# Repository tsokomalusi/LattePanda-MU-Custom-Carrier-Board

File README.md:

# LattePanda MU Custom Carrier Board

## High Speed PCB Design in KiCad

This repository contains a high-speed PCB design practice project created in KiCad
as part of the High Speed Design with KiCad course by D. Peter Dalmaris.

The primary goal of this project was to gain practical experience with modern
high-speed PCB layout techniques, signal integrity awareness, PCB stackup planning,
and manufacturability considerations.

# Project Background

The project workflow was inspired by the DFRobot LattePanda MU Carrier Board.

As part of the learning process:

- Existing PCB design constraints were studied
- PCB stackup parameters were imported into KiCad
- Routing practices from the reference design were analyzed
- High-speed layout techniques were explored through practical implementation
- Differential pair routing and length tuning techniques were practiced
- Teardrops were implemented throughout the PCB design process

PCIe functionality was not implemented, as the primary focus of the project
was PCB layout practice, signal routing exposure, and understanding high-speed
design workflows.

# 3D PCB Views

## Top Side

## Bottom Side

## Overview

# Technologies & Concepts

 USB 3.0 high-speed routing
- HDMI interface routing
- Gigabit Ethernet routing
- M.2 connector integration
- Differential pair routing and length tuning
- Controlled impedance awareness
- PCB stackup planning
- Return path considerations
- Teardrop implementation
- DFM analysis using NextPCB HQDFM tools

## Design Goals

The project focused on learning and applying:

- High-speed routing practices
- Differential pair management
- Signal integrity fundamentals
- PCB stackup awareness
- Manufacturability considerations

# PCB Stackup & Impedance Planning

The PCB stackup and impedance calculations were reviewed using the NextPCB
impedance calculator and stackup tools.

## Impedance Calculator

## NextPCB Stackup : Huaqiu04161H03-7628

## KiCad Stackup Configuration

## PCB Layout

### Full PCB Overview

# High-Speed Routing Examples

### USB 3.0 Routing

### Notes

- Differential pair routing applied to SuperSpeed signals
- Length tuning performed using KiCad tuning tools
- Pair spacing kept as consistent as possible
- Via transitions minimized where practical
- Teardrops applied throughout the routing process
- ESD protection placed close to connectors

### HDMI Routing

### Notes

- TMDS differential pair routing implemented
- Length tuning and routing symmetry considered
- High-speed signal paths prioritized
- Teardrops used to improve routing transitions

### Gigabit Ethernet Routing

### Notes

- Differential pair routing used for Ethernet signals
- Return path continuity considered
- Routing isolation considered where possible
- Length matching practices applied where practical

# Schematics
Detailed Schematic of this project can be found within this repository.
[Schematic](https://github.com/tsokomalusi/LattePanda-MU-Custom-Carrier-Board/blob/main/LattePandaMU_Carrier_Custom_Board.pdf)

## DFM Review

The design was analyzed using the NextPCB DFM tool to identify:

- trace width violations
- spacing violations
- drill clearance concerns
- manufacturability issues

This exercise helped reinforce practical PCB manufacturing constraints and layout discipline.

## Lessons Learned

- High-speed routing requires careful planning before layout begins
- PCB stackup directly affects routing constraints and impedance behavior
- Differential pair routing introduces spacing and tuning challenges
- Length tuning requires balancing routing quality and board space
- Reference designs are valuable learning tools for understanding real-world layouts
- DFM analysis helps identify manufacturing issues early in the design process
- Teardrops improve routing robustness and manufacturability
- High-speed PCB design involves both electrical and mechanical tradeoffs

## TOOLCHAIN

- KiCad — schematic capture and PCB layout
- Git & GitHub — version control and project hosting
- NextPCB HQDFM — DFM analysis and manufacturability review
  
## Disclaimer

This project was created for educational and portfolio purposes.

The board has not been fabricated or electrically validated.
PCIe - not implemented to reduce complexity at this stage, but can be future enhancement for V2.0 hopefully.

The DFM analysis is still work in progress.

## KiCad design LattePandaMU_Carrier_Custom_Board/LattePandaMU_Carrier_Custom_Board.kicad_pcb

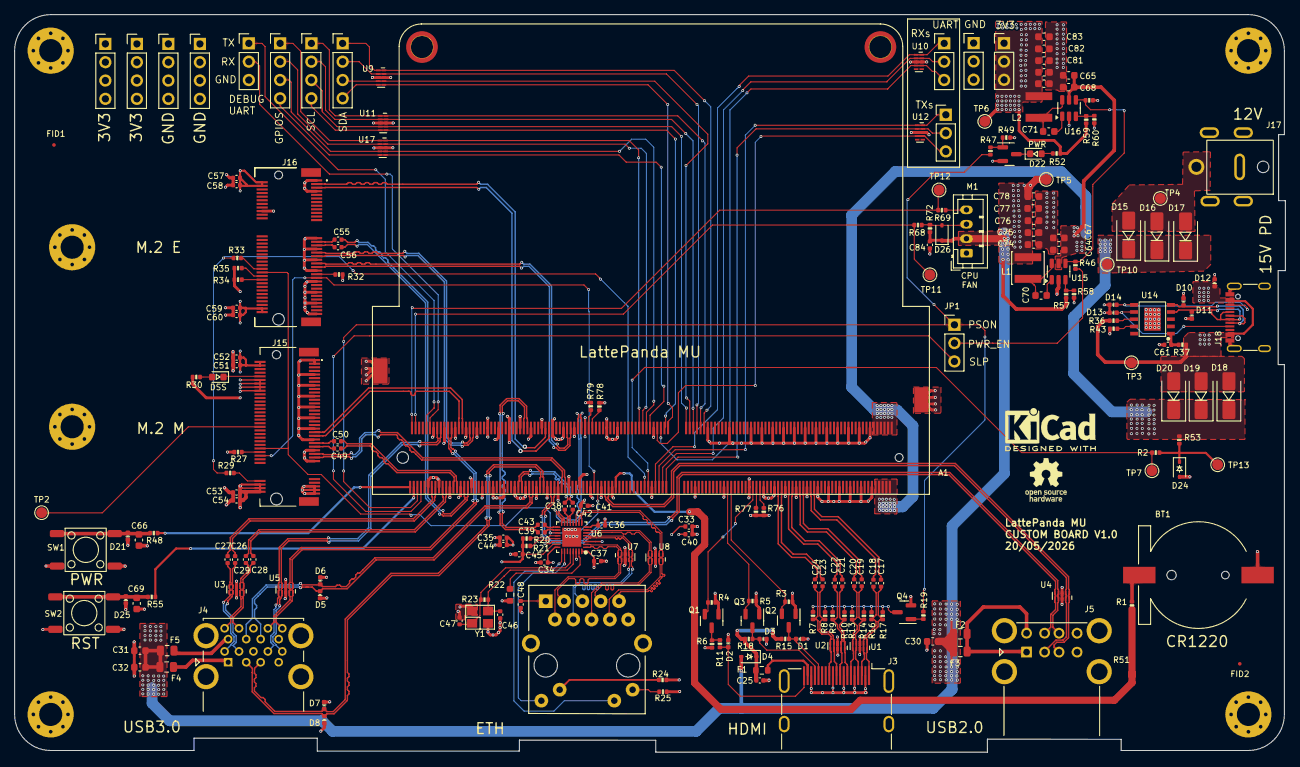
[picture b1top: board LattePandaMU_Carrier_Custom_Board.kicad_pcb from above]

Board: 4 copper layers, 176.1 x 102.2 mm, 218 parts (1 on the bottom side), 171 nets.

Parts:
A1: LattePanda_Mu; LattePanda_Module_H8.0mm_Horizontal
BT1: Battery_Cell; Battery_Holder_CR1220_S8411-45R
C17, C18, C19, C20, C21, C22, C23, C24, C25, C26, C27, C28, C29, C52, C53, C54, C58, C59, C60: 100nF/50V; C_0402_1005Metric
C30, C31, C32, C64, C65, C67, C68, C74, C75, C77, C78, C79, C80, C82, C83: 22u/10V; C_0603_1608Metric
C33, C34, C35, C36, C37, C38, C39, C40, C41, C42, C43, C45, C48, C84: 100n/50V; C_0402_1005Metric
C44: 10u/50V; C_0402_1005Metric
C46, C47: 12p/50V; C_0402_1005Metric
C49, C50, C55, C56: 220nF/50V; C_0402_1005Metric
C51, C57: 10uF/50V; C_0402_1005Metric
C61: 1u/16V; C_0402_1005Metric
C66, C69: 1u/16V; C_0603_1608Metric
C70, C71: 100n/50V; C_0603_1608Metric
C76, C81: 100n/10V; C_0603_1608Metric
D1, D2, D3, D5, D6, D7, D8: ESD5V0B03; D_0402_1005Metric
D4: 1N5819WS; D_SOD-323
D9: GREEN; LED_0603_1608Metric
D10, D11, D21, D25: ESD9B5.0ST5G; D_0402_1005Metric
D12, D13, D14: D_Zener; D_0402_1005Metric
D15, D16, D17, D18, D19, D20: D_Schottky; D_SMA
D22: LED; LED_0603_1608Metric
D24: 3V3 Izt=5mA; D_SOD-323
D26: 1N5819; D_SOD-323
F1: 6V/50mA; R_0603_1608Metric
F2, F3, F4, F5: 6V/1A; Fuse_0805_2012Metric
FID1, FID2: Fiducial; Fiducial_0.5mm_Mask1mm
H1, H2, H3, H4, H7, H8: MountingHole_Pad; MountingHole_3.2mm_M3_Pad_Via
H5, H6: MountingHole_Pad; MountingHole_3mm_M2_Pad_TopOnly
J1, J8, J10, J11, J14: Conn_01x03_Pin; PinHeader_1x03_P2.54mm_Vertical
J3: HDMI_A; HDMI_A_Molex_208658-1001_Horizontal
J4: USB3_A_Stacked; USB3_A_Molex_48406-0001_Horizontal_Stacked
J5: USB_A_Stacked; USB_A_CUI_UJ2-ADH-TH_Horizontal_Stacked
J6: RJ45_RB1-125B8G1A; RJ45_UDE_RB1-125B8G1A
J7, J9, J12, J13, J19, J20, J21: Conn_01x04_Pin; PinHeader_1x04_P2.54mm_Vertical
J15: Bus_M.2_Socket_M; PCIe_M.2_Connectors_P=0.5mm_H=4.2mm_KeyM
J16: Bus_M.2_Socket_E; PCIe_M.2_Connectors_P=0.5mm_H=4.2mm_KeyE
J17: Barrel_Jack_Switch; DC_Jack_DC007B_30V_10A
J18: USB_C_Receptacle_USB2.0_16P; USB_C_Receptacle_G-Switch_GT-USB-7010ASV
JP1: Jumper_3_Bridged12; PinHeader_1x03_P2.54mm_Vertical
L1, L2: 2u2/4.3A; L_Sunlord_SWPA4020S
M1: Fan_4pin; JST_PH_B4B-PH-K_1x04_P2.00mm_Vertical
Q1, Q2, Q3, Q4: 2SK3018; SOT-23
Q8: 2N7002; SOT-23
R1, R11, R37, R47: 1K/1%; R_0402_1005Metric
R2, R20, R21, R34, R35, R36, R49, R58, R78, R79: 10K/1%; R_0402_1005Metric
R3, R5, R15, R18, R30: 2.2K/1%; R_0402_1005Metric
R4, R23: 1M/1%; R_0402_1005Metric
R6: 21.5K/1%; R_0402_1005Metric
R7, R8, R9, R10, R13, R14, R16, R17, R24, R25: 470R/1%; R_0402_1005Metric
R19, R52, R53: 2K2/1%; R_0402_1005Metric
R22: 2K49/1%; R_0603_1608Metric
R27, R29, R32, R33: 0R/1%; R_0402_1005Metric
R43: 56K/1%; R_0402_1005Metric
R46, R48, R55, R69: 100R/1%; R_0402_1005Metric
R51, R76, R77: 100K/1%; R_0402_1005Metric
R57: 75K/1%; R_0402_1005Metric
R59: 21K5K/1%; R_0402_1005Metric
R60, R72: 4K7/1%; R_0402_1005Metric
R68: 21K5/1%; R_0402_1005Metric
SW1, SW2: SW_Push; SW_Push_6x6x6
TP2, TP3, TP4, TP5, TP6, TP7, TP10, TP11, TP12, TP13: TestPoint; TestPoint_Pad_D1.5mm
U1, U2, U3, U4, U5, U7, U8, U9, U10, U11, U12, U17: ULC0524P; Diodes_UDFN-10_1.0x2.5mm_P0.5mm
U6: RTL8111H-CG-RH; QFN-32-1EP_4x4mm_P0.4mm_EP2.65x2.65mm
U14: USB PD等快充协议受电芯片-CH224K-ESSOP10; ESSOP-10-1EP_3.9x5mm_P1.0mm_EP3.2x2.3
U15, U16: LM2734X; TSOT-23-6
Xigote_Log: LOGO; Footprint_logos
Y1: 25MHz; Crystal_SMD_3225-4Pin_3.2x2.5mm

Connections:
5V_HDMI_VCC: C25.1, D4.1 (K), F1.1, R15.1, R18.1
+1V0: C33.1, C34.1, C35.1, C36.1, C40.1, C44.1, U6.3 (AVDD10), U6.8 (AVDD10), U6.22 (DVDD10), U6.24 (REGOUT), U6.30 (AVDD10)
+3V3: C37.1, C41.1, C45.1, C51.1, C52.1, C53.1, C54.1, C57.1, C58.1, C59.1, C60.1, C79.2, C80.2, C81.2, C82.2, C83.2, J13.1, J13.2, J13.3, J13.4, J14.1, J14.2, J14.3, J15.2 (3.3V), J15.4 (3.3V), J15.12 (3.3V), J15.14 (3.3V), J15.16 (3.3V), J15.18 (3.3V), J15.70 (3.3V), J15.72 (3.3V), J15.74 (3.3V), J16.2 (3.3V), J16.4 (3.3V), J16.72 (3.3V), J16.74 (3.3V), J21.1, J21.2, J21.3, J21.4, L2.2, Q1.1 (G), Q2.1 (G), Q3.1 (G), R3.1, R4.1, R5.1, R20.2, R21.2, R24.2, R25.2, R30.2, R34.2, R35.2, R52.2, R59.2, TP6.1, U6.11 (AVDD33), U6.23 (VDDREG), U6.32 (AVDD33)
+5V: C30.2, C31.2, C32.2, C74.2, C75.2, C76.2, C77.2, C78.2, C84.1, D4.2 (A), D26.1 (K), F2.1, F3.1, F4.1, F5.1, L1.2, M1.2 (+), R57.2, R72.2, TP5.1
+12V: D15.2 (A), D16.2 (A), D17.2 (A), J17.1, TP4.1
+15V: D12.1 (K), D18.2 (A), D19.2 (A), D20.2 (A), J18.A4 (VBUS), J18.A9 (VBUS), J18.B4 (VBUS), J18.B9 (VBUS), R36.1, R37.1, TP3.1
+BATT: A1.115 (VBAT), R1.2
/Fan/FAN_1_PWM: A1.2 (FAN1_PWM), R69.2, TP12.1
/Fan/FAN_1_TAC: A1.4 (FAN1_TAC), R68.2, TP11.1
/GPIO/GPP_D0: A1.128 (GPP_D0), J19.1, U17.1, U17.10 (NC)
/GPIO/GPP_D1: A1.130 (GPP_D1), J19.2, U17.2, U17.9 (NC)
/GPIO/GPP_D2: A1.132 (GPP_D2), J19.3, U17.4, U17.7 (NC)
/GPIO/GPP_D3: A1.134 (GPP_D3), J19.4, U17.5, U17.6 (NC)
/GPIO/I2C2_SCL: A1.154 (I2C2_SCL), J9.1, U11.1, U11.10 (NC)
/GPIO/I2C2_SDA: A1.156 (I2C2_SDA), J7.1, U9.1, U9.10 (NC)
/GPIO/I2C3_SCL: A1.150 (I2C3_SCL), J9.2, U11.2, U11.9 (NC)
/GPIO/I2C3_SDA: A1.152 (I2C3_SDA), J7.2, U9.2, U9.9 (NC)
/GPIO/I2C4_SCL: A1.146 (I2C4_SCL), J9.3, U11.4, U11.7 (NC)
/GPIO/I2C4_SDA: A1.148 (I2C4_SDA), J7.3, U9.4, U9.7 (NC)
/GPIO/I2C5_SCL: A1.142 (I2C5_SCL), J9.4, U11.5, U11.6 (NC)
/GPIO/I2C5_SDA: A1.144 (I2C5_SDA), J7.4, U9.5, U9.6 (NC)
/GPIO/SOC_UART0_RX: A1.137 (UART0_RXD), J8.1, U10.1, U10.10 (NC)
/GPIO/SOC_UART0_TX: A1.139 (UART0_TXD), J10.1, U12.1, U12.10 (NC)
/GPIO/SOC_UART1_RX: A1.141 (UART1_RXD), J8.2, U10.2, U10.9 (NC)
/GPIO/SOC_UART1_TX: A1.143 (UART1_TXD), J10.2, U12.2, U12.9 (NC)
/GPIO/SOC_UART2_RX: A1.140 (UART2_RXD), J8.3, U10.4, U10.7 (NC)
/GPIO/SOC_UART2_TX: A1.138 (UART2_TXD), J10.3, U12.4, U12.7 (NC)
/Gigabit Ethernet/GbE_PCIe_CLK+: A1.94 (REFCLK4+), U6.15 (REFCLK_P)
/Gigabit Ethernet/GbE_PCIe_CLK-: A1.96 (REFCLK4-), U6.16 (REFCLK_N)
/Gigabit Ethernet/GbE_PCIe_RX+: A1.64 (HSIO6_RX+), C43.1
/Gigabit Ethernet/GbE_PCIe_RX-: A1.66 (HSIO6_RX-), C39.1
/Gigabit Ethernet/GbE_PCIe_TX+: A1.61 (HSIO6_TX+), C42.1
/Gigabit Ethernet/GbE_PCIe_TX-: A1.63 (HSIO6_TX-), C38.1
/Gigabit Ethernet/HSI+: C42.2, U6.13 (HSIP)
/Gigabit Ethernet/HSI-: C38.2, U6.14 (HSIN)
/Gigabit Ethernet/HSO+: C43.2, U6.17 (HSOP)
/Gigabit Ethernet/HSO-: C39.2, U6.18 (HSON)
/Gigabit Ethernet/MDI0+: J6.R2 (TD1+), U6.1 (MDIP0), U7.1, U7.10 (NC)
/Gigabit Ethernet/MDI0-: J6.R3 (TD1-), U6.2 (MDIN0), U7.2, U7.9 (NC)
/Gigabit Ethernet/MDI1+: J6.R4 (TD2+), U6.4 (MDIP1), U7.4, U7.7 (NC)
/Gigabit Ethernet/MDI1-: J6.R5 (TD2-), U6.5 (MDIN1), U7.5, U7.6 (NC)
/Gigabit Ethernet/MDI2+: J6.R6 (TD3+), U6.6 (MDIP2), U8.5, U8.6 (NC)
/Gigabit Ethernet/MDI2-: J6.R7 (TD3-), U6.7 (MDIN2), U8.4, U8.7 (NC)
/Gigabit Ethernet/MDI3+: J6.R8 (TD4+), U6.9 (MDIP3), U8.2, U8.9 (NC)
/Gigabit Ethernet/MDI3-: J6.R9 (TD4-), U6.10 (MDIN3), U8.1, U8.10 (NC)
/HDMI/DBI_B_TX0+: A1.217 (DDIB_TX0+), C17.1
/HDMI/DBI_B_TX0-: A1.215 (DDIB_TX0-), C18.1
/HDMI/DBI_B_TX1+: A1.211 (DDIB_TX1+), C19.1
/HDMI/DBI_B_TX1-: A1.209 (DDIB_TX1-), C20.1
/HDMI/DBI_B_TX2+: A1.205 (DDIB_TX2+), C21.1
/HDMI/DBI_B_TX2-: A1.203 (DDIB_TX2-), C22.1
/HDMI/DBI_B_TX3+: A1.199 (DDIB_TX3+), C23.1
/HDMI/DBI_B_TX3-: A1.197 (DDIB_TX3-), C24.1
/HDMI/DDC_SCL: D1.2 (A2), J3.15 (SCL), Q2.3 (D), R15.2
/HDMI/DDC_SDA: D3.2 (A2), J3.16 (SDA), Q3.3 (D), R18.2
/HDMI/DDI_B_DDC_SCL: A1.171 (DDIB_DDC_SCL), Q2.2 (S), R3.2
/HDMI/DDI_B_DDC_SDA: A1.169 (DDIB_DDC_SDA), Q3.2 (S), R5.2
/HDMI/DDI_B_HPD: A1.183 (DDIB_HPD), Q1.2 (S), R4.2
/HDMI/HPD: D2.2 (A2), J3.19 (HPD), R11.2
/HDMI/TMDS_CK+: C23.2, J3.10 (CK+), R8.1, U2.4, U2.7 (NC)
/HDMI/TMDS_CK-: C24.2, J3.12 (CK-), R7.1, U2.5, U2.6 (NC)
/HDMI/TMDS_D0+: C21.2, J3.7 (D0+), R10.1, U2.1, U2.10 (NC)
/HDMI/TMDS_D0-: C22.2, J3.9 (D0-), R9.1, U2.2, U2.9 (NC)
/HDMI/TMDS_D1+: C19.2, J3.4 (D1+), R14.1, U1.4, U1.7 (NC)
/HDMI/TMDS_D1-: C20.2, J3.6 (D1-), R13.1, U1.5, U1.6 (NC)
/HDMI/TMDS_D2+: C17.2, J3.1 (D2+), R17.1, U1.1, U1.10 (NC)
/HDMI/TMDS_D2-: C18.2, J3.3 (D2-), R16.1, U1.2, U1.9 (NC)
/LattePanda Module/HSIO_0_TX+: A1.13 (HSIO0_TX+), C27.1
/LattePanda Module/HSIO_0_TX-: A1.15 (HSIO0_TX-), C26.1
/LattePanda Module/HSIO_1_TX+: A1.19 (HSIO1_TX+), C29.1
/LattePanda Module/HSIO_1_TX-: A1.21 (HSIO1_TX-), C28.1
/LattePanda Module/HSIO_2_RX+: A1.28 (HSIO2_RX+), J15.43 (PERp0/SATA-B-)
/LattePanda Module/HSIO_2_RX-: A1.30 (HSIO2_RX-), J15.41 (PERn0/SATA-B+)
/LattePanda Module/HSIO_2_TX+: A1.25 (HSIO2_TX+), C49.1
/LattePanda Module/HSIO_2_TX-: A1.27 (HSIO2_TX-), C50.1
/LattePanda Module/HSIO_3_RX+: A1.34 (HSIO3_RX+), J16.41 (PERp0)
/LattePanda Module/HSIO_3_RX-: A1.36 (HSIO3_RX-), J16.43 (PERn0)
/LattePanda Module/HSIO_3_TX+: A1.31 (HSIO3_TX+), C55.1
/LattePanda Module/HSIO_3_TX-: A1.33 (HSIO3_TX-), C56.1
/LattePanda Module/REFCLK0+: A1.85 (REFCLK0+), J15.55 (REFCLKp)
/LattePanda Module/REFCLK0-: A1.87 (REFCLK0-), J15.53 (REFCLKn)
/LattePanda Module/REFCLK3+: A1.88 (REFCLK3+), J16.47 (REFCLKp0)
/LattePanda Module/REFCLK3-: A1.90 (REFCLK3-), J16.49 (REFCLKn0)
/LattePanda Module/SLS_S3: A1.7 (SLS_S3), JP1.3 (B)
/LattePanda Module/SUSCLK_WIFI: A1.131 (SUSCLK), R29.2, R33.1
/LattePanda Module/USB2_P7+: A1.76 (USB2_P7+), J16.3 (USB_D+)
/LattePanda Module/USB2_P7-: A1.78 (USB2_P7-), J16.5 (USB_D-)
/LattePanda Module/~PWR_SW: A1.1 (~PWRBTN), R48.1
/LattePanda Module/~RST_SW: A1.3 (~RSTBTN), R55.1
/M.2 M Key/CONN_PCIE_TX_0+: C55.2, J16.35 (PETp0)
/M.2 M Key/CONN_PCIE_TX_0-: C56.2, J16.37 (PETn0)
/M.2 M Key/CONN_PCIE_TX_1+: C49.2, J15.49 (PETp0/SATA-A+)
/M.2 M Key/CONN_PCIE_TX_1-: C50.2, J15.47 (PETn0/SATA-A-)
/M.2 M Key/~CLKREQE: J16.53 (~CLKREQ0), R32.1
/M.2 M Key/~CLKREQM: J15.52 (~CLKREQ), R27.1
/Power Supply/CC1: D13.1 (K), J18.A5 (CC1), U14.7 (CC1)
/Power Supply/CC2: D14.1 (K), J18.B5 (CC2), U14.6 (CC2)
/Power Supply/PWR_C_D+: D11.2 (A2), J18.A6 (D+), J18.B6 (D+), U14.4 (DP)
/Power Supply/PWR_C_D-: D10.2 (A2), J18.A7 (D-), J18.B7 (D-), U14.5 (DM)
/Power Supply/PWR_EN: R46.2, R51.2, U15.4 (EN), U16.4 (EN)
/USB 2.0 & 3.0/CON_USB1_D_N: A1.109 (USB2_P5-), J5.2 (D1-), U4.2, U4.9 (NC)
/USB 2.0 & 3.0/CON_USB1_D_P: A1.111 (USB2_P5+), J5.3 (D1+), U4.1, U4.10 (NC)
/USB 2.0 & 3.0/CON_USB2_D_N: A1.79 (USB2_P3-), J5.6 (D2-), U4.5, U4.6 (NC)
/USB 2.0 & 3.0/CON_USB2_D_P: A1.81 (USB2_P3+), J5.7 (D2+), U4.4, U4.7 (NC)
/USB 2.0 & 3.0/CON_USB3_D_N: A1.73 (USB2_P2-), D8.2 (A2), J4.2 (D1-)
/USB 2.0 & 3.0/CON_USB3_D_P: A1.75 (USB2_P2+), D7.2 (A2), J4.3 (D1+)
/USB 2.0 & 3.0/CON_USB3_SSRX_N: A1.18 (HSIO0_RX-), J4.5 (SSRX1-), U5.4, U5.7 (NC)
/USB 2.0 & 3.0/CON_USB3_SSRX_P: A1.16 (HSIO0_RX+), J4.6 (SSRX1+), U5.5, U5.6 (NC)
/USB 2.0 & 3.0/CON_USB3_SSTX_N: C26.2, J4.8 (SSTX1-), U3.4, U3.7 (NC)
/USB 2.0 & 3.0/CON_USB3_SSTX_P: C27.2, J4.9 (SSTX1+), U3.5, U3.6 (NC)
/USB 2.0 & 3.0/CON_USB4_D_N: A1.67 (USB2_P1-), D6.2 (A2), J4.11 (D2-)
/USB 2.0 & 3.0/CON_USB4_D_P: A1.69 (USB2_P1+), D5.2 (A2), J4.12 (D2+)
/USB 2.0 & 3.0/CON_USB4_SSRX_N: A1.24 (HSIO1_RX-), J4.14 (SSRX2-), U5.1, U5.10 (NC)
/USB 2.0 & 3.0/CON_USB4_SSRX_P: A1.22 (HSIO1_RX+), J4.15 (SSRX2+), U5.2, U5.9 (NC)
/USB 2.0 & 3.0/CON_USB4_SSTX_N: C28.2, J4.17 (SSTX2-), U3.1, U3.10 (NC)
/USB 2.0 & 3.0/CON_USB4_SSTX_P: C29.2, J4.18 (SSTX2+), U3.2, U3.9 (NC)
/~PLT_RST: A1.105 (~PLTRST), J15.50 (~PERST), J16.52 (~PERST0), U6.19 (PERSTB)
/~PWR_LED/PSON: A1.5 (SLS_S0), JP1.1 (A), R19.2, R47.1
/~WAKE: A1.103 (~WAKE), J15.54 (~PEWAKE), J16.55 (~PEWAKE0)
GND: A1.11 (GND), A1.14 (GND), A1.17 (GND), A1.20 (GND), A1.23 (GND), A1.26 (GND), A1.29 (GND), A1.32 (GND), A1.35 (GND), A1.38 (GND), A1.41 (GND), A1.44 (GND), A1.47 (GND), A1.50 (GND), A1.53 (GND), A1.56 (GND), A1.59 (GND), A1.62 (GND), A1.65 (GND), A1.68 (GND), A1.71 (GND), A1.74 (GND), A1.77 (GND), A1.80 (GND), A1.83 (GND), A1.86 (GND), A1.89 (GND), A1.92 (GND), A1.95 (GND), A1.98 (GND), A1.101 (GND), A1.107 (GND), A1.110 (GND), A1.113 (GND), A1.116 (GND), A1.135 (GND), A1.136 (GND), A1.151 (GND), A1.158 (GND), A1.167 (GND), A1.170 (GND), A1.181 (GND), A1.182 (GND), A1.188 (GND), A1.189 (GND), A1.194 (GND), A1.195 (GND), A1.200 (GND), A1.201 (GND), A1.206 (GND), A1.207 (GND), A1.212 (GND), A1.213 (GND), A1.218 (GND), A1.219 (GND), A1.224 (GND), A1.225 (GND), A1.230 (GND), A1.231 (GND), A1.236 (GND), A1.237 (GND), A1.242 (GND), A1.243 (GND), A1.248 (GND), A1.249 (GND), A1.MP (Mountinge_Pads), BT1.2 (-), C25.2, C30.1, C31.1, C32.1, C33.2, C34.2, C35.2, C36.2, C37.2, C40.2, C41.2, C44.2, C45.2, C46.1, C47.1, C48.1, C51.2, C52.2, C53.2, C54.2, C57.2, C58.2, C59.2, C60.2, C61.1, C64.1, C65.2, C66.1, C67.1, C68.2, C69.1, C74.1, C75.1, C76.1, C77.1, C78.1, C79.1, C80.1, C81.1, C82.1, C83.1, C84.2, D1.1 (A1), D2.1 (A1), D3.1 (A1), D5.1 (A1), D6.1 (A1), D7.1 (A1), D8.1 (A1), D10.1 (A1), D11.1 (A1), D12.2 (A), D13.2 (A), D14.2 (A), D21.1 (A1), D24.2 (A), D25.1 (A1), H1.1, H2.1, H3.1, H4.1, H5.1, H6.1, H7.1, H8.1, J1.3, J3.2 (D2S), J3.5 (D1S), J3.8 (D0S), J3.11 (CKS), J3.17 (GND), J3.SH, J4.4 (GND1), J4.7 (DRAIN1), J4.13 (GND2), J4.16 (DRAIN2), J4.19 (SHIELD), J5.4 (GND1), J5.8 (GND2), J5.9 (Shield), J6.R10 (GND), J6.SH, J11.1, J11.2, J11.3, J12.1, J12.2, J12.3, J12.4, J15.1 (GND), J15.3 (GND), J15.9 (GND), J15.15 (GND), J15.21 (GND), J15.27 (GND), J15.33 (GND), J15.39 (GND), J15.45 (GND), J15.51 (GND), J15.57 (GND), J15.71 (GND), J15.73 (GND), J15.75 (GND), J16.1 (GND), J16.7 (GND), J16.18 (GND), J16.33 (GND), J16.39 (GND), J16.45 (GND), J16.51 (GND), J16.57 (GND), J16.63 (GND), J16.69 (GND), J16.75 (GND), J17.2, J17.3, J18.A1 (GND), J18.A12 (GND), J18.B1 (GND), J18.B12 (GND), J18.S1 (SHIELD), J20.1, J20.2, J20.3, J20.4, M1.1 (-), Q4.2 (S), Q8.2 (S), R6.2, R22.1, R27.2, R32.2, R43.2, R49.1, R51.1, R58.1, R60.1, R76.1, R77.1, R78.1, R79.1, SW1.2, SW2.2, U1.3 (VSS), U1.8 (VSS), U2.3 (VSS), U2.8 (VSS), U3.3 (VSS), U3.8 (VSS), U4.3 (VSS), U4.8 (VSS), U5.3 (VSS), U5.8 (VSS), U6.33 (GND), U7.3 (VSS), U7.8 (VSS), U8.3 (VSS), U8.8 (VSS), U9.3 (VSS), U9.8 (VSS), U10.3 (VSS), U10.8 (VSS), U11.3 (VSS), U11.8 (VSS), U12.3 (VSS), U12.8 (VSS), U14.0 (GND), U15.2 (GND), U16.2 (GND), U17.3 (VSS), U17.8 (VSS), Y1.2, Y1.4
unnamed: A1.12 (SIO_UART_RX), J1.2
unnamed: A1.10 (SIO_UART_TX), J1.1
unnamed: A1.187 (TCP0_HPD), R76.2
unnamed: A1.185 (TCP1_HPD), R77.2
unnamed: A1.133 (~BIOS_SEL), R2.1, TP7.1
unnamed: A1.100 (~CLKREQ3), R79.2
unnamed: A1.102 (~CLKREQ4), R78.2
unnamed: BT1.1 (+), R1.1
unnamed: D9.2 (A), R30.1
unnamed: D9.1 (K), J15.10 (DAS/~DSS/~LED1)
unnamed: C66.2, D21.2 (A2), R48.2, SW1.1
unnamed: D22.2 (A), R52.1
unnamed: D22.1 (K), Q8.3 (D)
unnamed: C69.2, D25.2 (A2), R55.2, SW2.1
unnamed: D26.2 (A), M1.3 (Tacho), R68.1, R72.1
unnamed: F1.2, J3.18 (+5V)
unnamed: F4.2, J4.1 (VBUS1)
unnamed: F5.2, J4.10 (VBUS2)
unnamed: F2.2, F3.2, J5.1 (VBUS1), J5.5 (VBUS2)
unnamed: C48.2, J6.R1 (CT)
unnamed: J6.L1, R25.1
unnamed: J6.L3, R24.1
unnamed: J15.38 (DEVSLP), TP2.1
unnamed: J15.68 (SUSCLK), R29.1
unnamed: J16.50 (SUSCLK), R33.2
unnamed: J16.56 (~W_DISABLE1), R34.1
unnamed: J16.54 (~W_DISABLE2), R35.1
unnamed: JP1.2 (C), R46.1
unnamed: M1.4 (PWM), R69.1
unnamed: Q1.3 (D), R6.1, R11.1
unnamed: Q4.3 (D), R7.2, R8.2, R9.2, R10.2, R13.2, R14.2, R16.2, R17.2
unnamed: Q4.1 (G), R19.1
unnamed: Q8.1 (G), R47.2, R49.2
unnamed: C47.2, R23.1, U6.28 (CKXTAL1), Y1.1
unnamed: C46.2, R23.2, U6.29 (CKXTAL2), Y1.3
unnamed: R20.1, U6.20 (ISOLATEB)
unnamed: R21.1, U6.21 (LANWAKEB)
unnamed: J6.L4, U6.26 (LED1)
unnamed: J6.L2, U6.25 (LED2)
unnamed: R22.2, U6.31 (RSET)
unnamed: R43.1, U14.9 (CFG1)
unnamed: R36.2, U14.8 (VBUS)
unnamed: C61.2, R37.2, U14.1 (VDD)
unnamed: C70.1, U15.1 (BOOST)
unnamed: R57.1, R58.2, U15.3 (FB)
unnamed: C70.2, L1.1, U15.6 (SW)
unnamed: C71.1, U16.1 (BOOST)
unnamed: R59.1, R60.2, U16.3 (FB)
unnamed: C71.2, L2.1, U16.6 (SW)
VDC: A1.250 (VIN), A1.251 (VIN), A1.252 (VIN), A1.253 (VIN), A1.254 (VIN), A1.255 (VIN), A1.256 (VIN), A1.257 (VIN), A1.258 (VIN), A1.259 (VIN), A1.260 (VIN), C64.2, C65.1, C67.2, C68.1, D15.1 (K), D16.1 (K), D17.1 (K), D18.1 (K), D19.1 (K), D20.1 (K), R53.2, TP10.1, U15.5 (VIN), U16.5 (VIN)
VPullup: D24.1 (K), R2.2, R53.1, TP13.1

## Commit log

2026-05-25 Adding PCB Layout
2026-05-25 adding usb3.0 routing
2026-05-25 ADDING HDMI and ETH routing
2026-05-25 adding PCB STACKUP AND IMPEDANCE CALCULATOR
